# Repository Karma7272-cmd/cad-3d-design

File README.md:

# 3D Designs

This repository contains my 3D design projects and models.

## Contents

* Mechanical 3D Models
* Product Designs
* Engineering Components
* Prototypes
* CAD Designs

## Software

* Fusion 360
* SolidWorks
* FreeCAD
* Blender

## Purpose

This repository is used to store, organize, and showcase my 3D design work.

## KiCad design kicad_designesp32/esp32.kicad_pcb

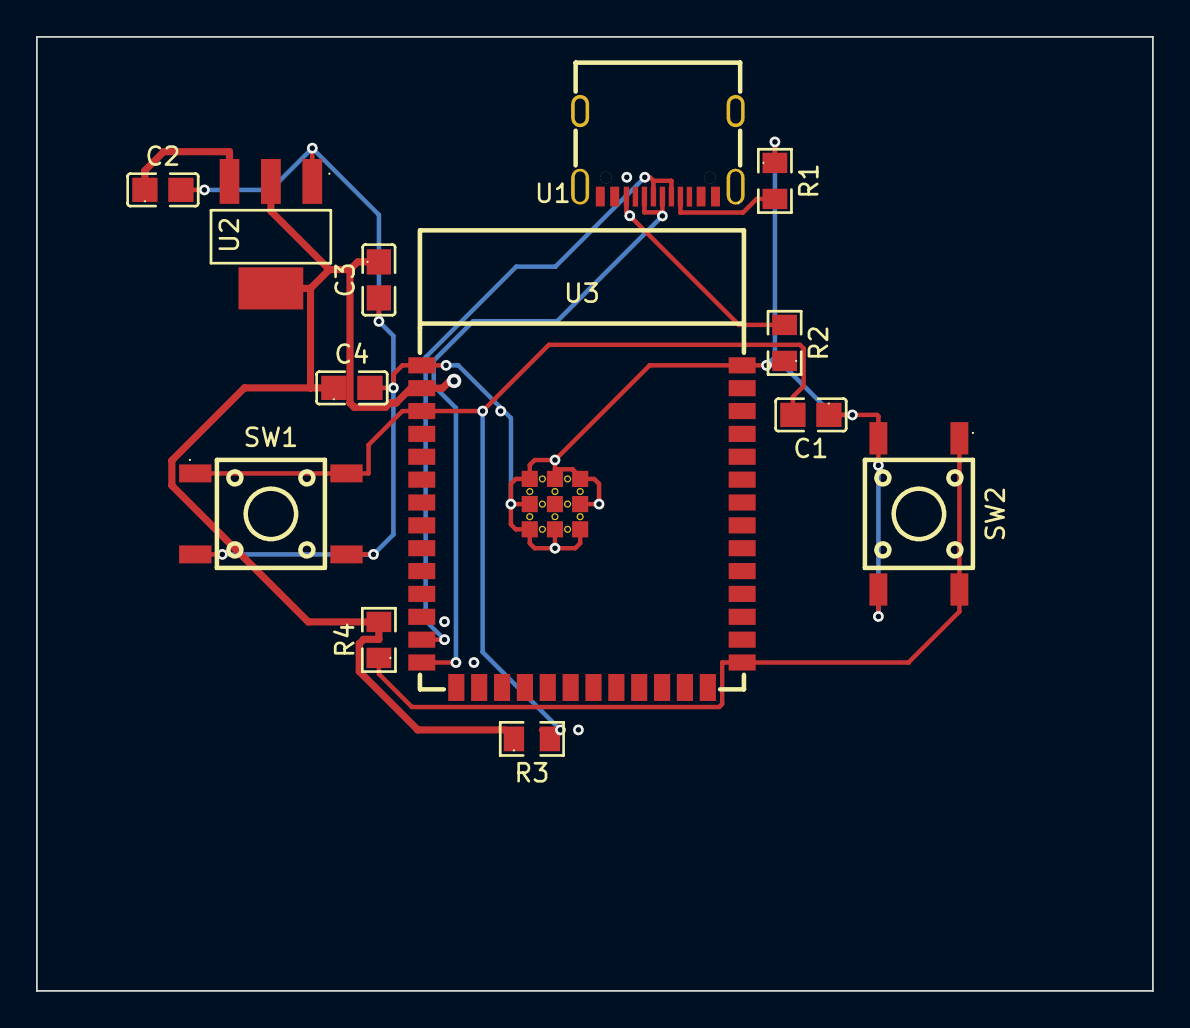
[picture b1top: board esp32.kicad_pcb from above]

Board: 2 copper layers, 62.0 x 53.0 mm, 13 parts (0 on the bottom side), 9 nets.

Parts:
C1, C2: 10uF; C0805
C3: 22uF; C0805
C4: 100nF; C0805
R1, R2: 5.1k; R0805
R3, R4: 10k; R0805
SW1, SW2: HX-6X6X7.3-TP FT SQUARE BUTTON; SW-SMD_4P-L6.0-W6.0-P4.50-LS9.0-H7.3
U1: USB-TYPE-C-019; TYPE-C-SMD_HX-TYPE-C-16PIN
U2: AMS1117-3.3; SOT-223-3_L6.5-W3.4-P2.30-LS7.0-BR
U3: ESP32-S3-WROOM-1-N8; WIFIM-SMD_ESP32-S3-WROOM-1-N8

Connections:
+3.3V: C3.1, C4.1, R3.1, R4.2, U2.2, U2.4, U3.2
BOOT_BTN: R4.1, SW2.1, SW2.2, U3.27
GND: C1.1, C2.2, C3.2, C4.2, R1.1, R2.1, SW1.3, SW1.4, SW2.3, SW2.4, U2.1, U3.1, U3.40, U3.41
N_0A4563B6: R1.2, U1.A5
N_136A54AC: R2.2, U1.B5
RESET_BTN: C1.2, R3.2, SW1.1, SW1.2, U3.3
USB_D_N: U1.A7, U1.B7, U3.13
USB_D_P: U1.A6, U1.B6, U3.14
VBUS: C2.1, U2.3
